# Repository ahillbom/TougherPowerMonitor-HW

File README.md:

### What is this?

Power monitor with three channels, each capable of continuous 10A and 24V. It is compatible with both Arduino and Feather, and is based on a popular INA3221. The power monitor is more robust compared to other modules based on this IC. Each channel has proper RC filtering with TVS diodes to prevent INA3221 from being destroyed by transients, and to eliminate glitches. Pluggable screw terminals are rated for 15A, and can handle 12 to 30 AWG wires.

The third channel has a TPS1HB08A power switch, to be able to disconnect the load.
The board can also provide power to the Feather or Arduino from the first channel via a built-in buck converter.

### Block diagram

### Schematics

### Assembled board

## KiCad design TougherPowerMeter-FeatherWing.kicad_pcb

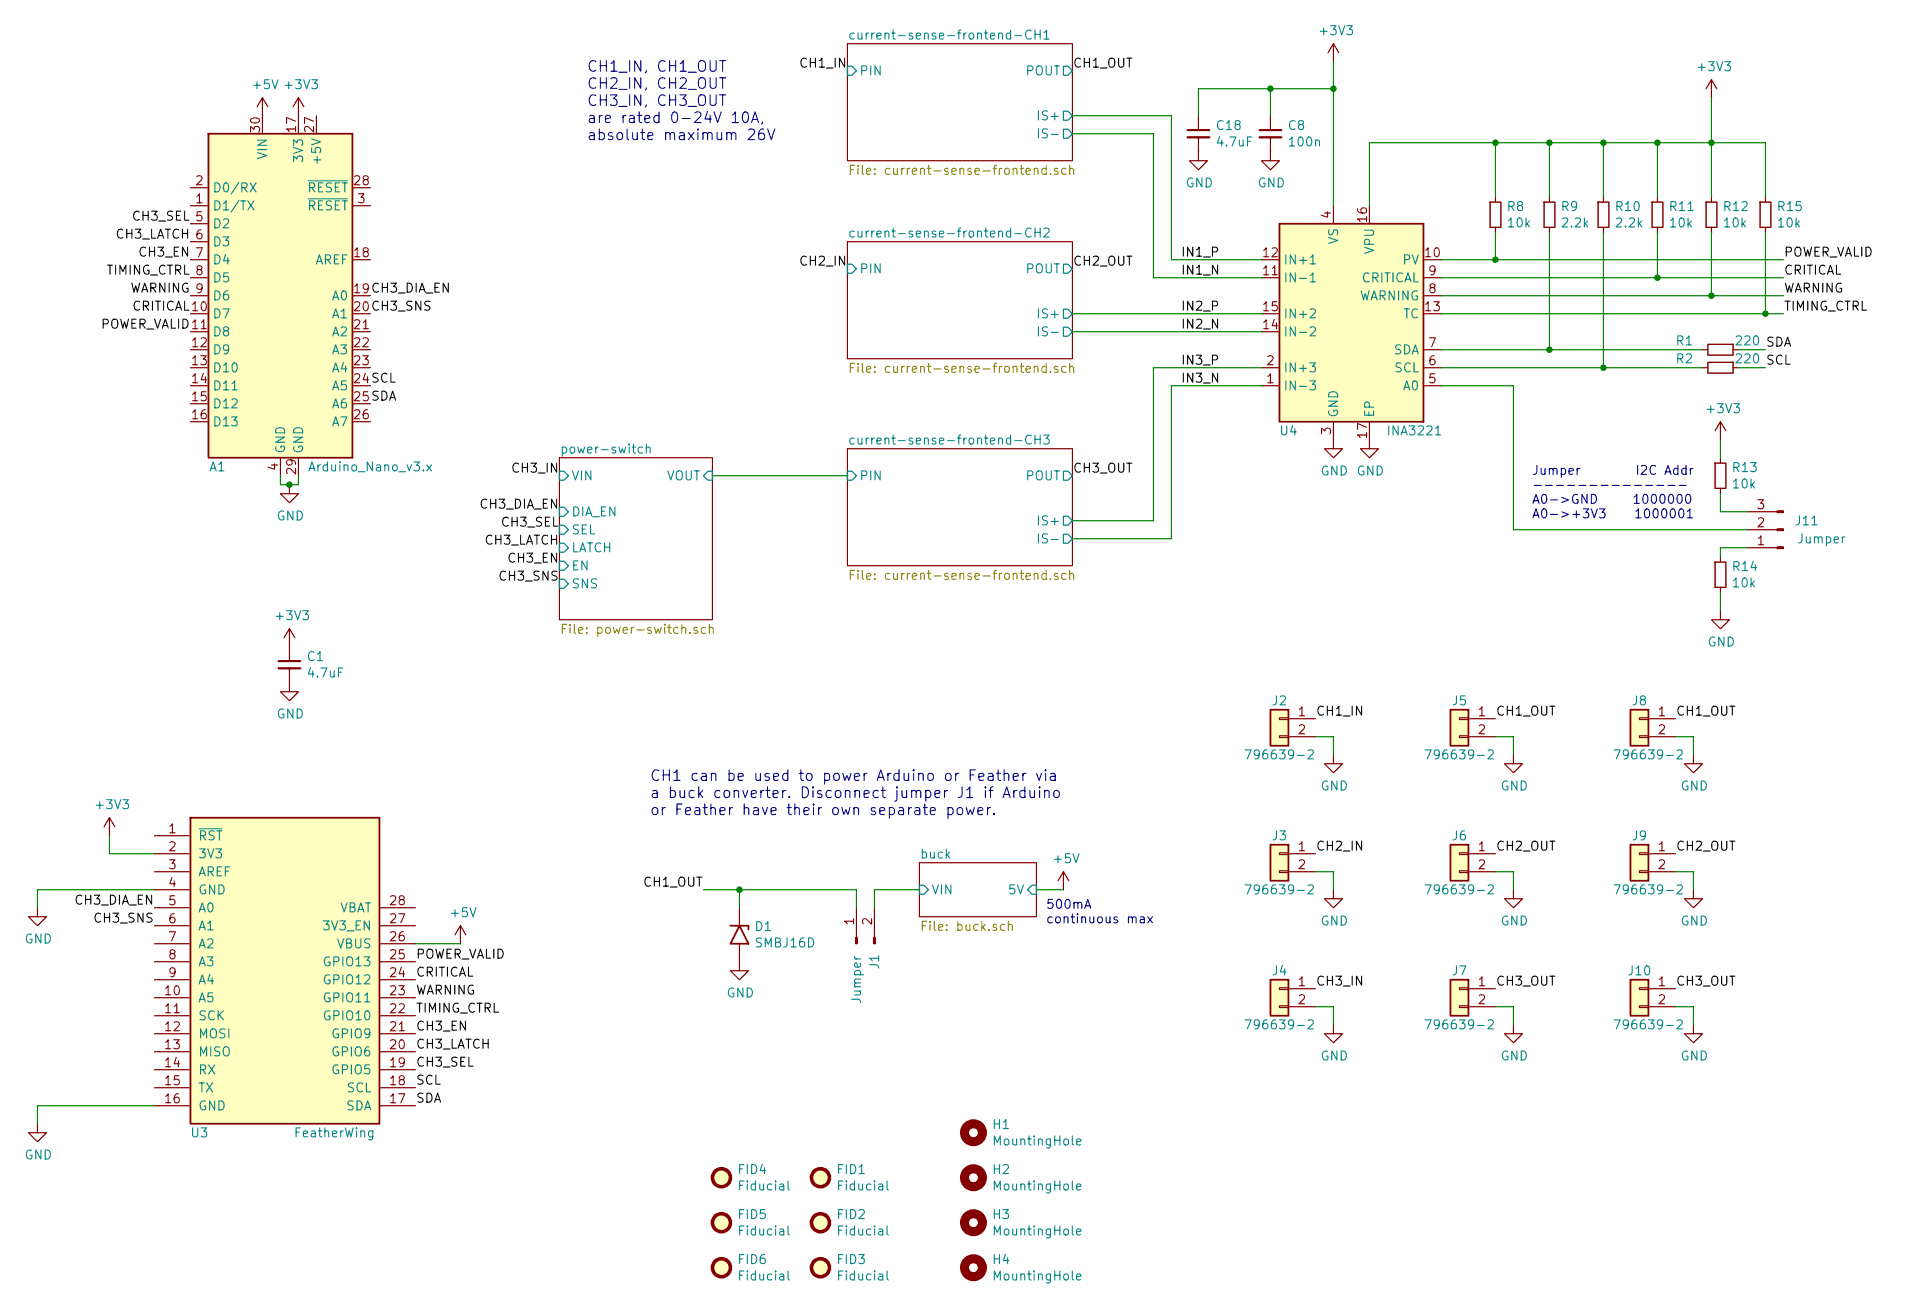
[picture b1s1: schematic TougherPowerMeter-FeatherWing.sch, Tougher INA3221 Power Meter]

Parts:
A1: Arduino_Nano_v3.x; Arduino_Nano_NoSilk
C1, C18: 4.7uF; C_0603_1608Metric
C8: 100n; C_0603_1608Metric
D1: SMBJ16D; D_SMB
FID1, FID2, FID3, FID4, FID5, FID6: Fiducial; Fiducial_1.5mm_Mask4.5mm
H1, H2, H3, H4: MountingHole; MountingHole_3.2mm_M3_Pad_Via
J1: Jumper; PinHeader_1x02_P2.54mm_Vertical
J2, J3, J4, J5, J6, J7, J8, J9, J10: 796639-2; TE_796639-2
J11: Jumper; PinHeader_1x03_P2.54mm_Vertical
R1, R2: 220; R_0603_1608Metric
R8, R11, R12, R13, R14, R15: 10k; R_0603_1608Metric
R9, R10: 2.2k; R_0603_1608Metric
U3: FeatherWing; FeatherWing_NoMH
U4: INA3221; Texas_RGV_S-PVQFN-N16_EP2.1x2.1mm

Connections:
+3V3: A1.17 (3V3), C1.1, C8.1, C18.1, R8.1, R9.1, R10.1, R11.1, R12.1, R13.1, R15.1, U3.2 (3V3), U4.4 (VS), U4.16 (VPU)
+5V: A1.30 (VIN), U3.26 (VBUS); also elsewhere on the board
/CH1_IN: J2.1; also elsewhere on the board
/CH1_OUT: D1.1 (A1), J1.1, J5.1, J8.1; also elsewhere on the board
/CH2_IN: J3.1; also elsewhere on the board
/CH2_OUT: J6.1, J9.1; also elsewhere on the board
/CH3_DIA_EN: A1.19 (A0), U3.5 (A0); also elsewhere on the board
/CH3_EN: A1.7 (D4), U3.21 (GPIO9); also elsewhere on the board
/CH3_IN: J4.1; also elsewhere on the board
/CH3_LATCH: A1.6 (D3), U3.20 (GPIO6); also elsewhere on the board
/CH3_OUT: J7.1, J10.1; also elsewhere on the board
/CH3_SEL: A1.5 (D2), U3.19 (GPIO5); also elsewhere on the board
/CH3_SNS: A1.20 (A1), U3.6 (A1); also elsewhere on the board
/CRITICAL: A1.10 (D7), R11.2, U3.24 (GPIO12), U4.9 (CRITICAL)
/IN1_N: U4.11 (IN-1); also elsewhere on the board
/IN1_P: U4.12 (IN+1); also elsewhere on the board
/IN2_N: U4.14 (IN-2); also elsewhere on the board
/IN2_P: U4.15 (IN+2); also elsewhere on the board
/IN3_N: U4.1 (IN-3); also elsewhere on the board
/IN3_P: U4.2 (IN+3); also elsewhere on the board
/POWER_VALID: A1.11 (D8), R8.2, U3.25 (GPIO13), U4.10 (PV)
/SCL: A1.24 (A5), R2.1, U3.18 (SCL)
/SDA: A1.25 (A6), R1.1, U3.17 (SDA)
/TIMING_CTRL: A1.8 (D5), R15.2, U3.22 (GPIO10), U4.13 (TC)
/WARNING: A1.9 (D6), R12.2, U3.23 (GPIO11), U4.8 (WARNING)
/buck/VIN: J1.2; also elsewhere on the board
GND: A1.4 (GND), A1.29 (GND), C1.2, C8.2, C18.2, D1.2 (A2), J2.2, J3.2, J4.2, J5.2, J6.2, J7.2, J8.2, J9.2, J10.2, R14.2, U3.4 (GND), U3.16 (GND), U4.3 (GND), U4.17 (EP); also elsewhere on the board
unnamed: J11.1, R14.1
unnamed: J11.2, U4.5 (A0)
unnamed: J11.3, R13.2
unnamed: R1.2, R9.2, U4.7 (SDA)
unnamed: R2.2, R10.2, U4.6 (SCL)

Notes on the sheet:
Jumper I2C Addr -------------- A0->GND 1000000 A0->+3V3 1000001
CH1_IN, CH1_OUT CH2_IN, CH2_OUT CH3_IN, CH3_OUT are rated 0-24V 10A, absolute maximum 26V
CH1 can be used to power Arduino or Feather via a buck converter. Disconnect jumper J1 if Arduino or Feather have their own separate power.
500mA continuous max

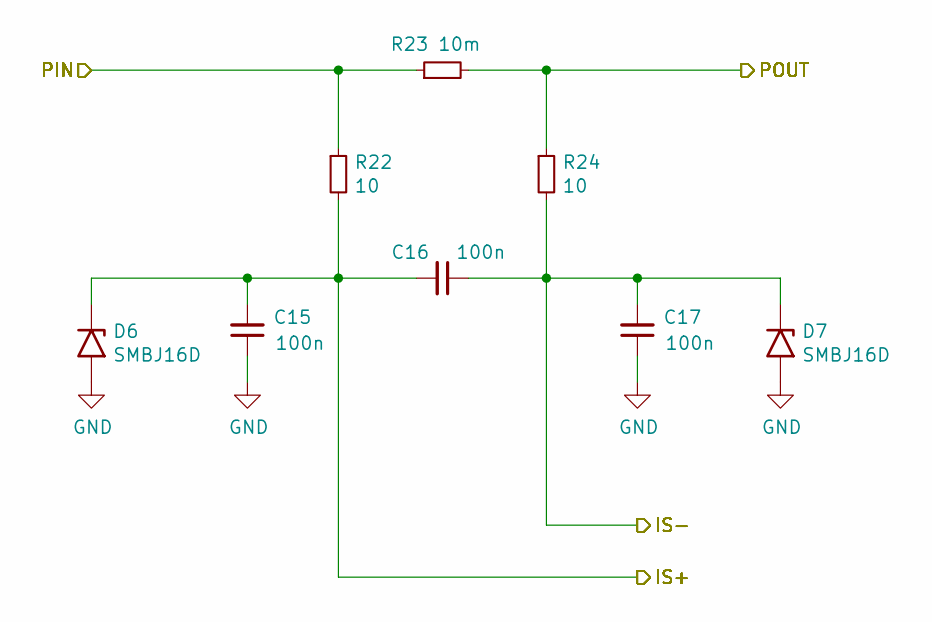
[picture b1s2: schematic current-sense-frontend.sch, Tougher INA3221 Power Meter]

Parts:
C9, C10, C11: 100n; C_0603_1608Metric
D2, D3: SMBJ16D; D_SMB
R16, R18: 10; R_0603_1608Metric
R17: 10m; R_2512_6332Metric

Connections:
/CH3_OUT: R17.2, R18.1; also elsewhere on the board
/IN3_N: C10.1, C11.2, D3.1 (A1), R18.2; also elsewhere on the board
/IN3_P: C9.2, C10.2, D2.1 (A1), R16.2; also elsewhere on the board
/current-sense-frontend-CH3/PIN: R16.1, R17.1; also elsewhere on the board
GND: C9.1, C11.1, D2.2 (A2), D3.2 (A2); also elsewhere on the board

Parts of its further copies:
C12, C13, C14, C15, C16, C17: 100n; C_0603_1608Metric
D4, D5, D6, D7: SMBJ16D; D_SMB
R19, R21, R22, R24: 10; R_0603_1608Metric
R20, R23: 10m; R_2512_6332Metric

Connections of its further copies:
/CH1_IN: R22.1, R23.1; also elsewhere on the board
/CH1_OUT: R23.2, R24.1; also elsewhere on the board
/CH2_IN: R19.1, R20.1; also elsewhere on the board
/CH2_OUT: R20.2, R21.1; also elsewhere on the board
/IN1_N: C16.1, C17.2, D7.1 (A1), R24.2; also elsewhere on the board
/IN1_P: C15.2, C16.2, D6.1 (A1), R22.2; also elsewhere on the board
/IN2_N: C13.1, C14.2, D5.1 (A1), R21.2; also elsewhere on the board
/IN2_P: C12.2, C13.2, D4.1 (A1), R19.2; also elsewhere on the board
GND: C12.1, C14.1, C15.1, C17.1, D4.2 (A2), D5.2 (A2), D6.2 (A2), D7.2 (A2); also elsewhere on the board

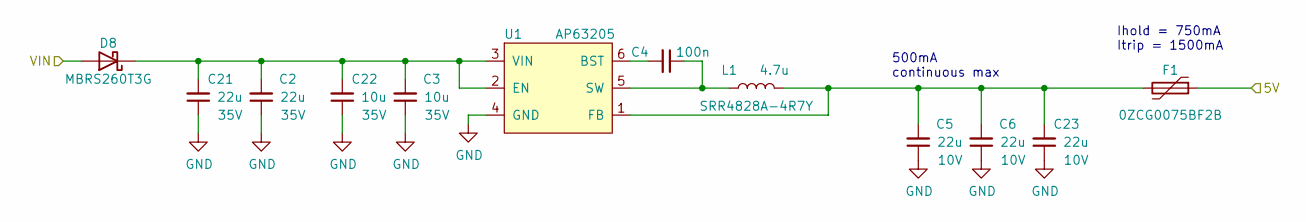
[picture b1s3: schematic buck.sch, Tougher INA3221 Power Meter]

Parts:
C2, C21: 22u; C_1210_3225Metric; Voltage 35V
C3, C22: 10u; C_1206_3216Metric; Voltage 35V
C4: 100n; R_0603_1608Metric
C5, C6, C23: 22u; C_0805_2012Metric; Voltage 10V
D8: D_Schottky; D_SMB; Part Number MBRS260T3G
F1: 0ZCG0075BF2B; Fuse_1812_4532Metric; Part Number 0ZCG0075BF2B
L1: 4.7u; L_Bourns_SRR1210A; Part Number SRR4828A-4R7Y
U1: AP63205; TSOT-23-6

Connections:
+5V: F1.1; also elsewhere on the board
/buck/VIN: D8.2 (A); also elsewhere on the board
GND: C2.1, C3.1, C5.1, C6.1, C21.1, C22.1, C23.1, U1.4 (GND); also elsewhere on the board
unnamed: C2.2, C3.2, C21.2, C22.2, D8.1 (K), U1.2 (EN), U1.3 (VIN)
unnamed: C4.1, L1.1, U1.5 (SW)
unnamed: C4.2, U1.6 (BST)
unnamed: C5.2, C6.2, C23.2, F1.2, L1.2, U1.1 (FB)

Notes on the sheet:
500mA continuous max
Ihold = 750mA Itrip = 1500mA

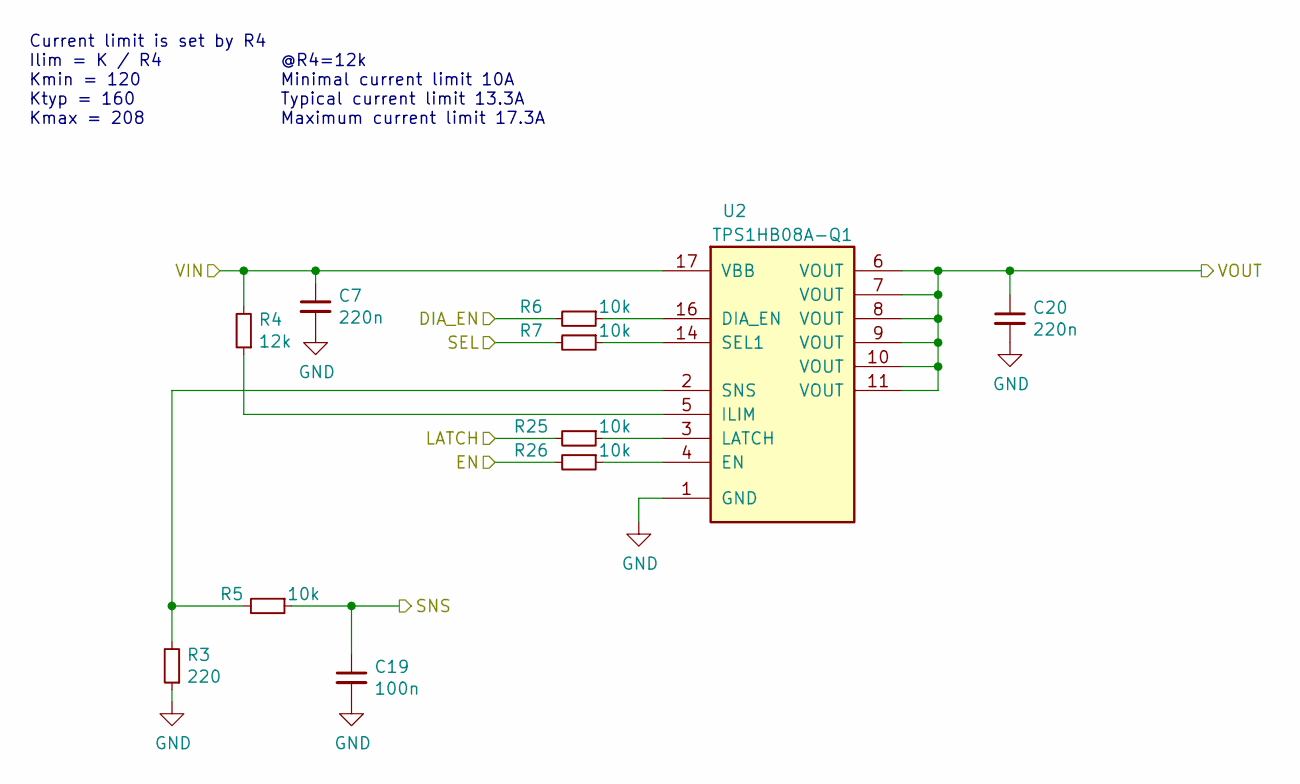
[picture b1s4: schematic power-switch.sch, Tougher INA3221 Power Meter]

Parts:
C7, C20: 220n; C_0603_1608Metric
C19: 100n; R_0603_1608Metric
R3: 220; R_0603_1608Metric
R4: 12k; R_0603_1608Metric
R5, R6, R7, R25, R26: 10k; R_0603_1608Metric
U2: TPS1HB08A-Q1; HTSSOP-16-1EP_4.4x5mm_P0.65mm_EP3.4x5mm

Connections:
/CH3_DIA_EN: R6.2; also elsewhere on the board
/CH3_EN: R26.2; also elsewhere on the board
/CH3_IN: C7.1, R4.2, U2.17 (VBB); also elsewhere on the board
/CH3_LATCH: R25.2; also elsewhere on the board
/CH3_SEL: R7.2; also elsewhere on the board
/CH3_SNS: C19.1, R5.1; also elsewhere on the board
/current-sense-frontend-CH3/PIN: C20.1, U2.6 (VOUT), U2.7 (VOUT), U2.8 (VOUT), U2.9 (VOUT), U2.10 (VOUT), U2.11 (VOUT); also elsewhere on the board
GND: C7.2, C19.2, C20.2, R3.1, U2.1 (GND); also elsewhere on the board
unnamed: R3.2, R5.2, U2.2 (SNS)
unnamed: R4.1, U2.5 (ILIM)
unnamed: R6.1, U2.16 (DIA_EN)
unnamed: R7.1, U2.14 (SEL1)
unnamed: R25.1, U2.3 (LATCH)
unnamed: R26.1, U2.4 (EN)

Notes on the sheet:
Current limit is set by R4 Ilim = K / R4 Kmin = 120 Ktyp = 160 Kmax = 208
@R4=12k Minimal current limit 10A Typical current limit 13.3A Maximum current limit 17.3A

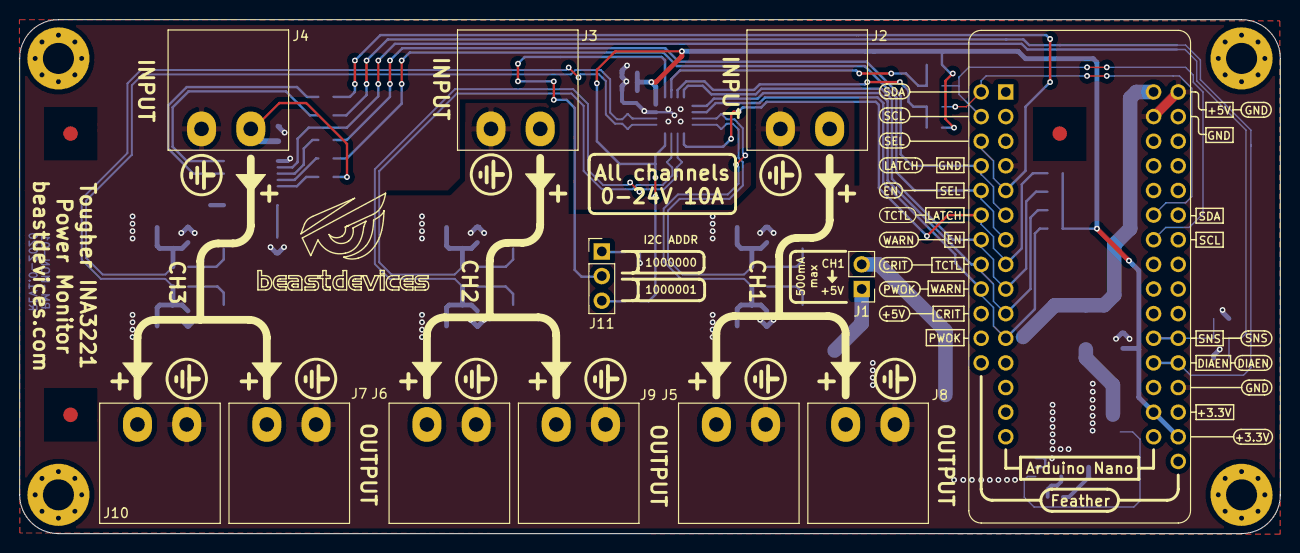
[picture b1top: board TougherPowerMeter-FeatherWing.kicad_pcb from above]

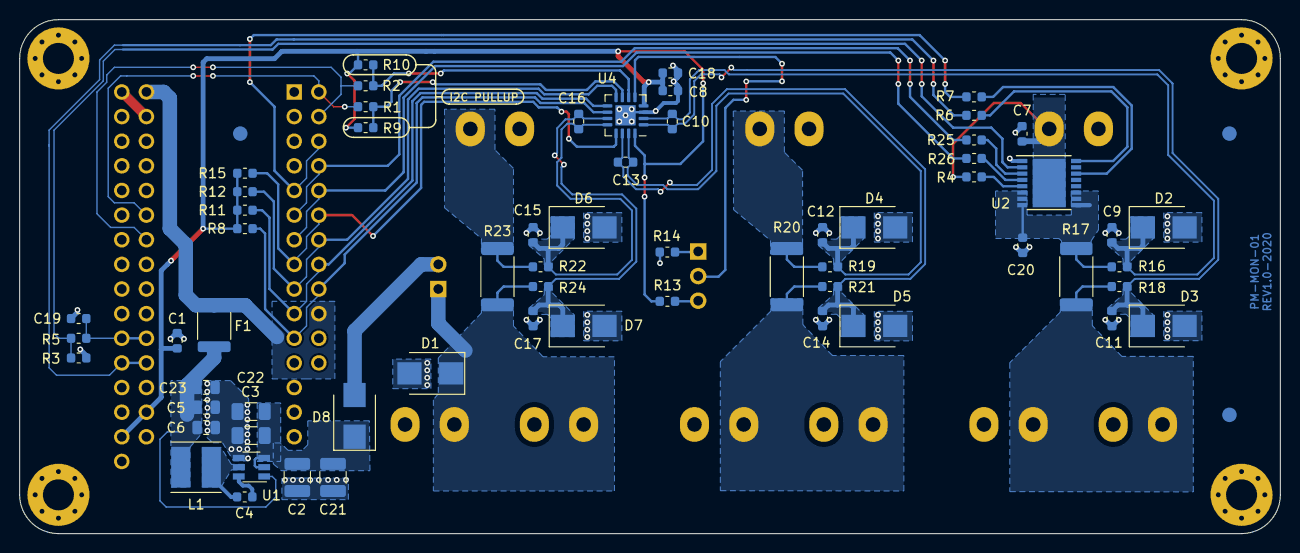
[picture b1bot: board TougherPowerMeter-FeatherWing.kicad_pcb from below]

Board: 2 copper layers, 130.0 x 53.0 mm, 85 parts (65 on the bottom side), 43 nets.

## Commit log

2020-09-05 Finish design
2020-09-05 Add fiducials, fix aesthetics in schematics
2020-09-05 Add schematics PDF and 3D renderings of PBA
2020-09-05 Add comment to schematics:
    CH1 can be used to power Arduino or Feather via
    a buck converter. Disconnect jumper J1 if Arduino
    or Feather have their own separate power.
2020-09-09 Add 3D renderings and update exported schematics
2020-09-09 Generate Gerber files (rev1.0-2020)
2020-09-09 Add block diagram
2020-09-09 Add README.md
2020-09-14 Add manufacturers, part numbers, and supplier links
2020-09-22 Change part number for the current sense resistor
2020-09-22 Update schematics exports
2021-04-03 Add photos of assembled PBA v1.0
2021-04-03 Replace render with photos in README
2021-05-13 Add submodule for the KiCad libraries.
    Add submodule for the KiCad libraries and change
    references to the libraries.
